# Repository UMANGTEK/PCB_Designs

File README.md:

This Repository consists of all the final versions of PCB designs made by me.

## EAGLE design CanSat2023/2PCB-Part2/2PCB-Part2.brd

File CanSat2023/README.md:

This folder consistes of the design files of flight computer for CANSAT competetion 2023. This is my first ever design of PCB which is completely designed by me me and was used on the actual cansat during launch.
Due to size restriction the computer was divided into two parts:

PART 1 - Consists of micro-controller, actuators and pins for power supply for the whole flight computer.

PART 2 - Consists of sensors operating through I2C and UART, some actuators which could fit in part 1 has also been added .

My objective while desiging this PCB was to keep microcontrollers, actuators and main power supply in same board as all actuators indivisually require independent signal from micro-controller, while I2C is a common
signal for I2C operable devices, this reduced the wires used to connect two parts. 

All the sensors used in the computer were pre fabricated, hence I did not consider the impedence while designing and worked with the default parameters. I had started working on this PCB by the end of 1-1 and wasn't aware with importance of trace width and kept an arbitary value of 0.5 mm for all connections. 

Both the PCB's are a 2 - Layered PCB, designed on free version of EAGLE software.

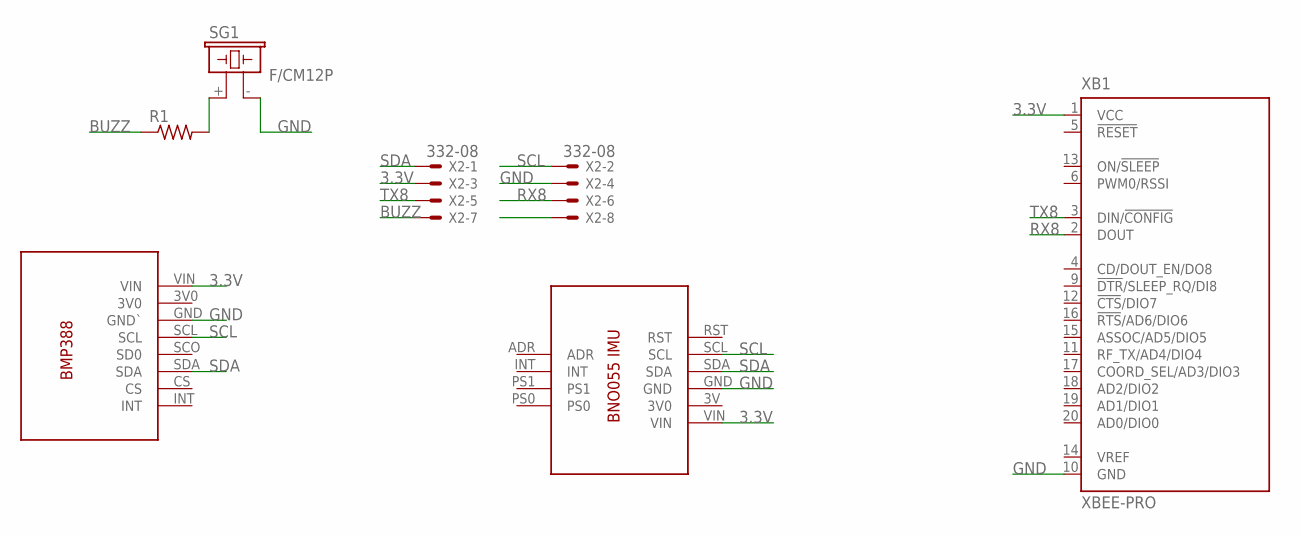
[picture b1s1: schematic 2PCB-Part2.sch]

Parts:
R1: R-US_0207/10; 0207/10
SG1: F/CM12P
U$1: BNO055
U$2: BMP388
X2: 332-08
XB1: XBEE-PRO

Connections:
3.3V: U$1.VIN, U$2.VIN, X2.3, XB1.1 (VCC)
BUZZ: R1.1, X2.7
GND: SG1.- (2), U$1.GND, U$2.GND (GND`), X2.4, XB1.10 (GND)
unnamed: R1.2, SG1.+ (1)
RX8: X2.6, XB1.2 (DOUT)
SCL: U$1.SCL, U$2.SCL, X2.2
SDA: U$1.SDA, U$2.SDA, X2.1
TX8: X2.5, XB1.3 (DIN/!CONFIG)

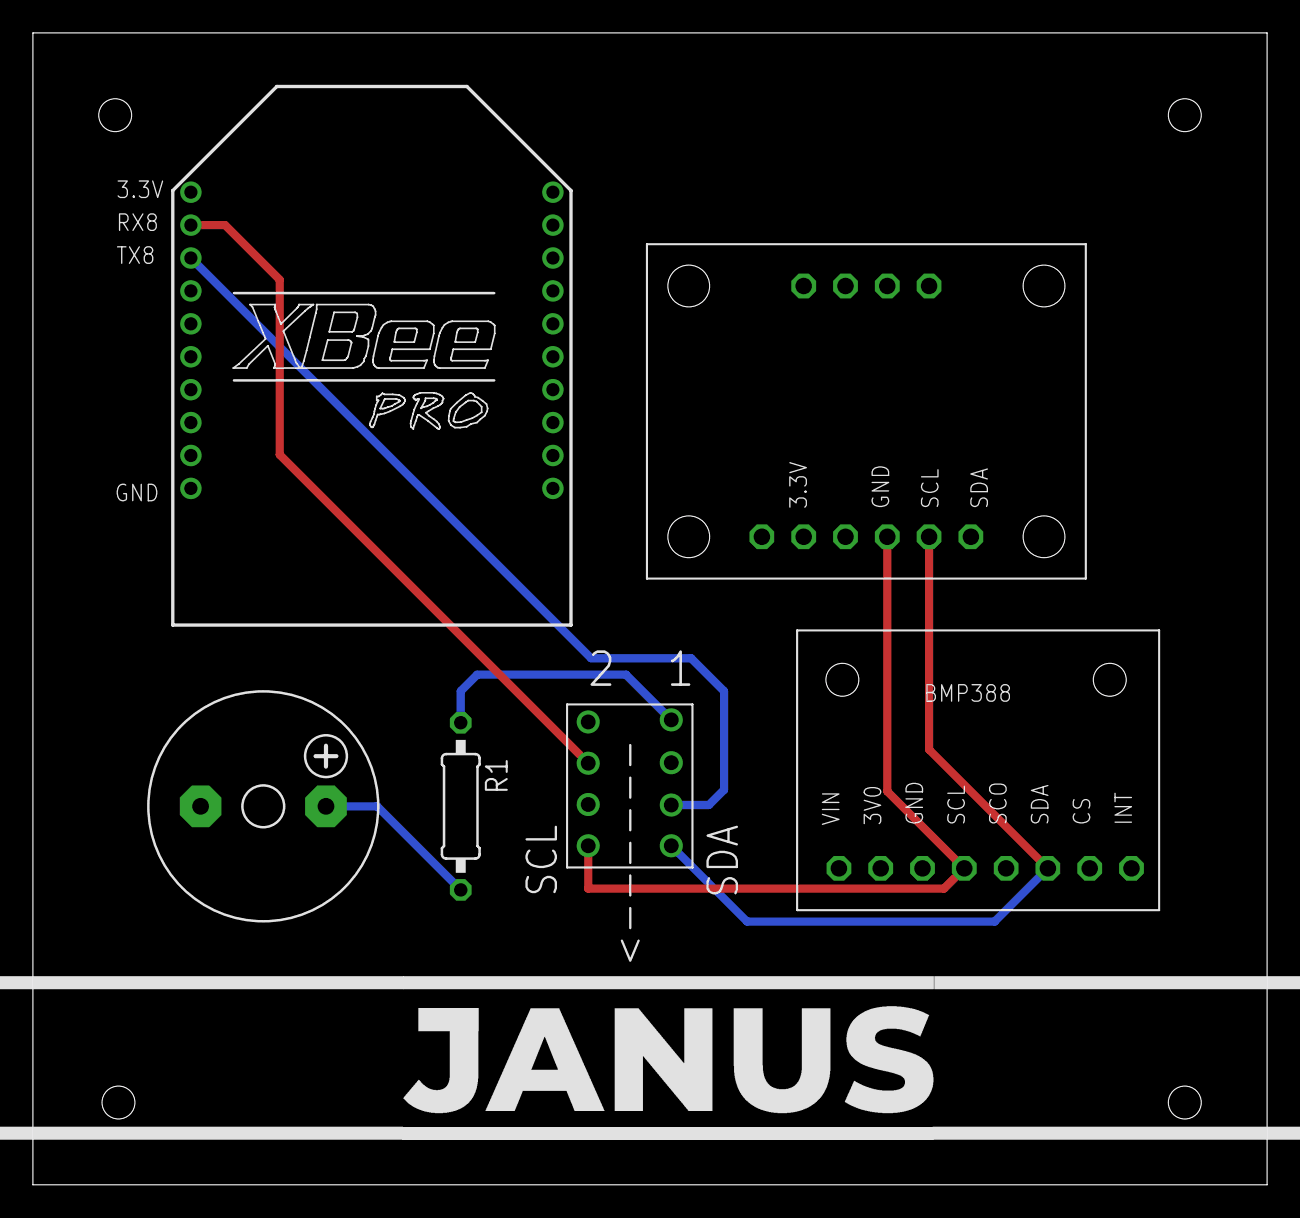
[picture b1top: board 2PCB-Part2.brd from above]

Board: 2 copper layers, 75.0 x 70.0 mm, 6 parts (0 on the bottom side), 8 nets.

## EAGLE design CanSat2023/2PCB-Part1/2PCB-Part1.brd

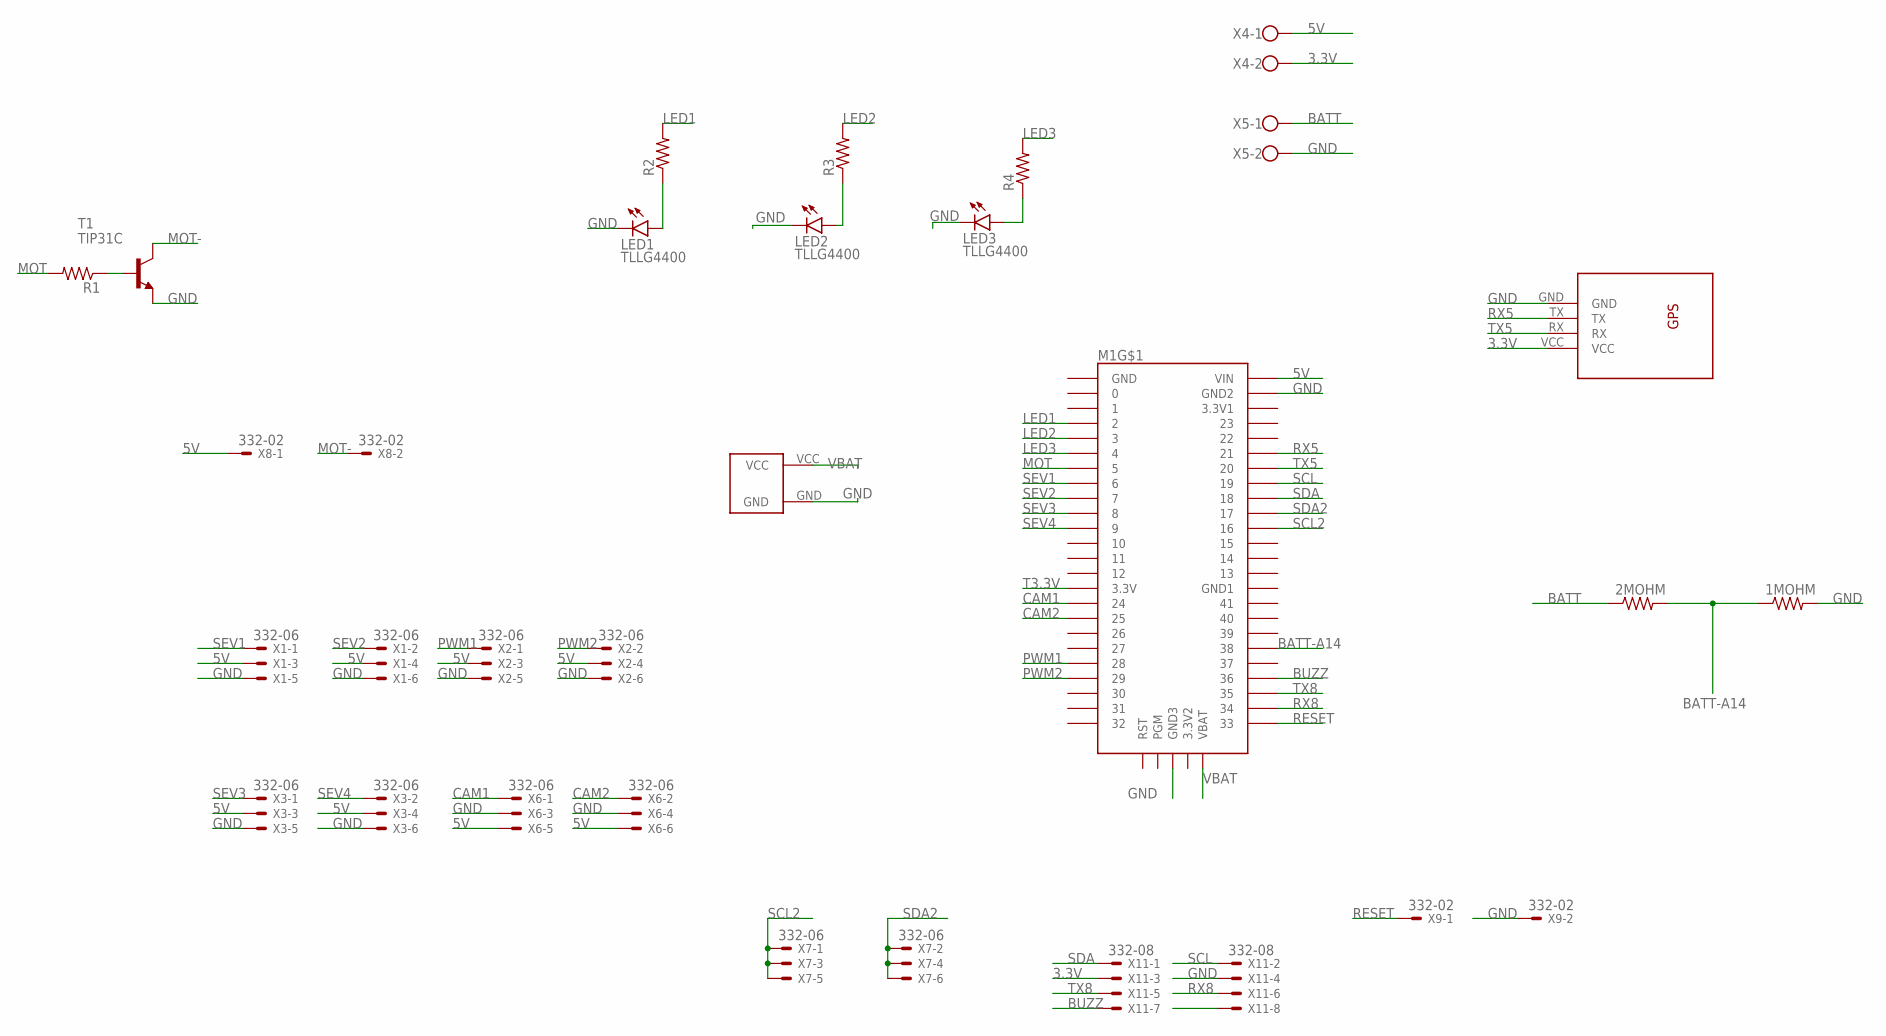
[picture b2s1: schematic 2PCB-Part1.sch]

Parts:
1MOHM, 2MOHM: R-US_0207/10; 0207/10
LED1, LED2, LED3: TLLG4400; LED3MM
M1: TEENSY4.1
R1, R2, R3, R4: R-US_0207/10; 0207/10
T1: TIP31C; TO220
U$1: GPS
U$2: CR2032; CR2032-20MM
X1, X2, X3, X6, X7: 332-06
X4, X5: W237-102
X8, X9: 332-02
X11: 332-08

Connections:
3.3V: U$1.VCC, X4.2, X11.3
5V: M1.VIN, X1.3, X1.4, X2.3, X2.4, X3.3, X3.4, X4.1, X6.5, X6.6, X8.1
BATT: 2MOHM.1, X5.1
BATT-A14: 1MOHM.1, 2MOHM.2, M1.38
BUZZ: M1.36, X11.7
CAM1: M1.24, X6.1
CAM2: M1.25, X6.2
GND: 1MOHM.2, LED1.K (C), LED2.K (C), LED3.K (C), M1.AGND (GND2), M1.GND2 (GND3), T1.3 (E), U$1.GND, U$2.GND, X1.5, X1.6, X2.5, X2.6, X3.5, X3.6, X5.2, X6.3, X6.4, X9.2, X11.4
LED1: M1.2, R2.2
LED2: M1.3, R3.2
LED3: M1.4, R4.2
MOT: M1.5, R1.2
MOT-: T1.2 (C), X8.2
unnamed: LED1.A, R2.1
unnamed: LED2.A, R3.1
unnamed: LED3.A, R4.1
unnamed: R1.1, T1.1 (B)
PWM1: M1.28, X2.1
PWM2: M1.29, X2.2
RESET: M1.33, X9.1
RX5: M1.21/A7 (21), U$1.TX
RX8: M1.34, X11.6
SCL: M1.19/A5/SCL (19), X11.2
SCL2: M1.16/A2 (16), X7.1, X7.3, X7.5
SDA: M1.18/A4/SDA (18), X11.1
SDA2: M1.17/A3 (17), X7.2, X7.4, X7.6
SEV1: M1.6, X1.1
SEV2: M1.7, X1.2
SEV3: M1.8, X3.1
SEV4: M1.9, X3.2
T3.3V: M1.3V3 (3.3V)
TX5: M1.20/A6 (20), U$1.RX
TX8: M1.35, X11.5
VBAT: M1.VBAT, U$2.VCC

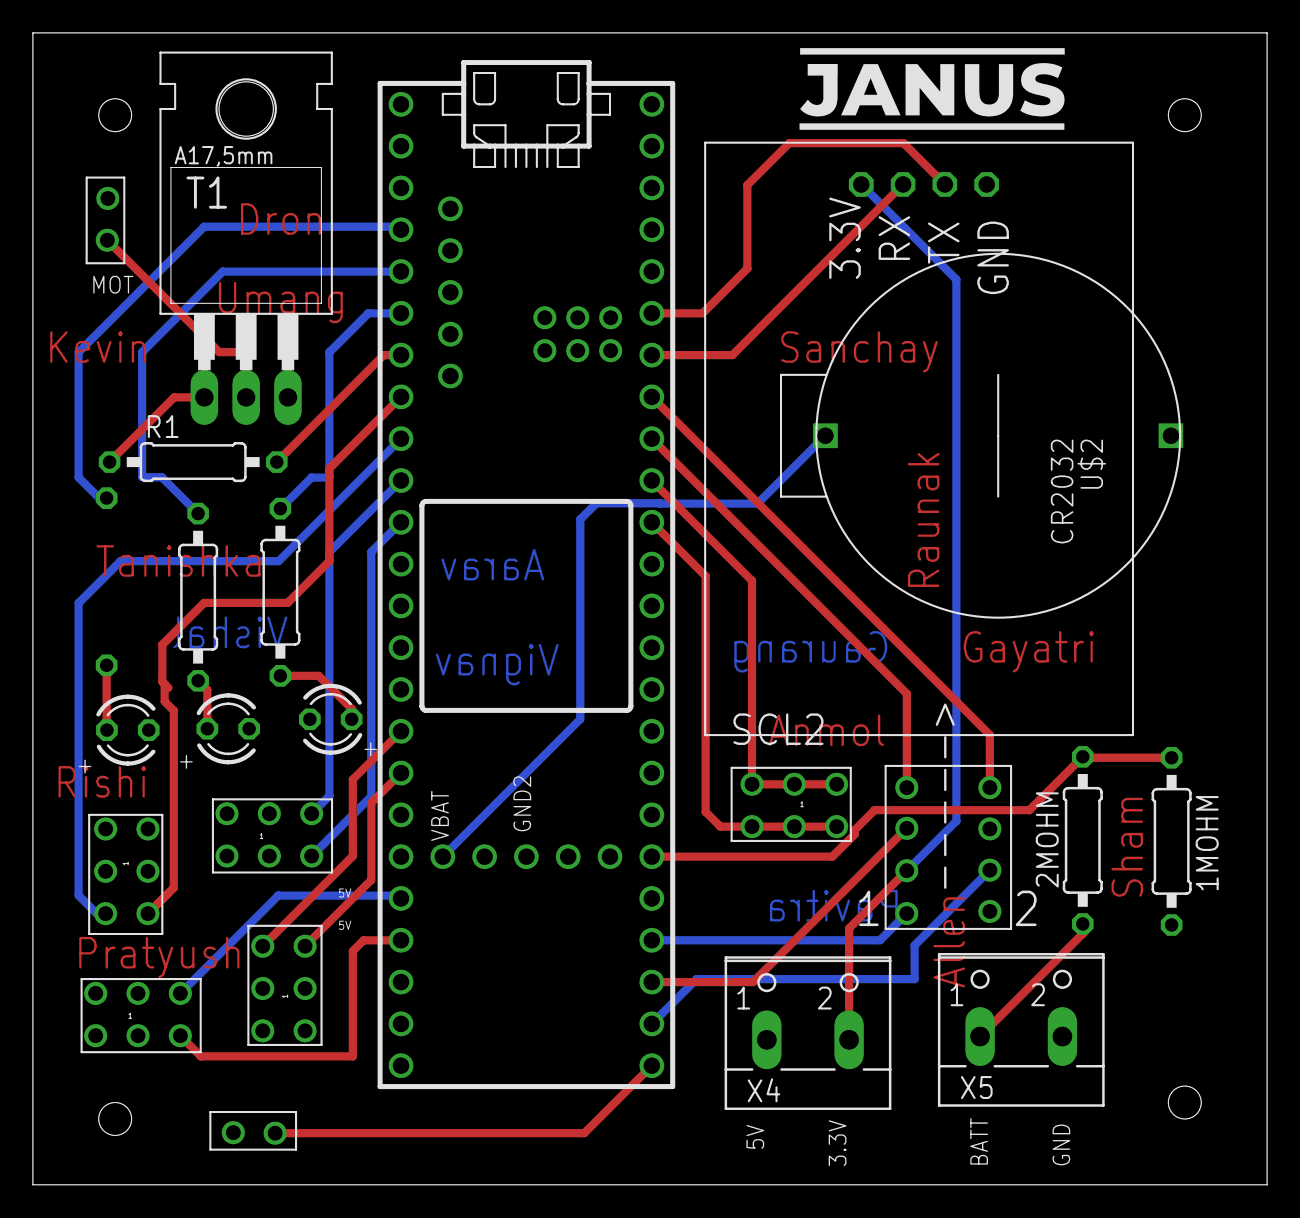
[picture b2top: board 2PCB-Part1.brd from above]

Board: 2 copper layers, 75.0 x 70.0 mm, 23 parts (1 on the bottom side), 33 nets.

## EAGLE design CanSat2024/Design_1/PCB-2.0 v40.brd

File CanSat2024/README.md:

These are the PCB designs for CanSat 2024, a total of 5 revisions were made in design. 2nd Revision was given for printing, learning from which, improvements were made and finally 5th revision was given for final print.

Design 1- This was a drastic improvement from the computer I made for 2023. This was designed in such a way that we only needed to connect battries and main switch, battery charging and power distribution components like
buck convertors were integrated in the design itself. Unlike last year, where we had to remove battry for charging and buck convertors were placed externally, this had it all on board. The battery which we were using are 
2x NCR18650B cells connected in series.

Design 2- Overall idea remained the same as design - 1 some improvements were made in connectors which made it more user friendly, and a overvoltage protection for microcontroller as also added without which the controller
kept on getting burn due to voltage rising above 3.3V as the pins were 3.3v tolerant.

This time I took care of trace width as per the current requirement for various components on board the flight computer which can be seen on design files.

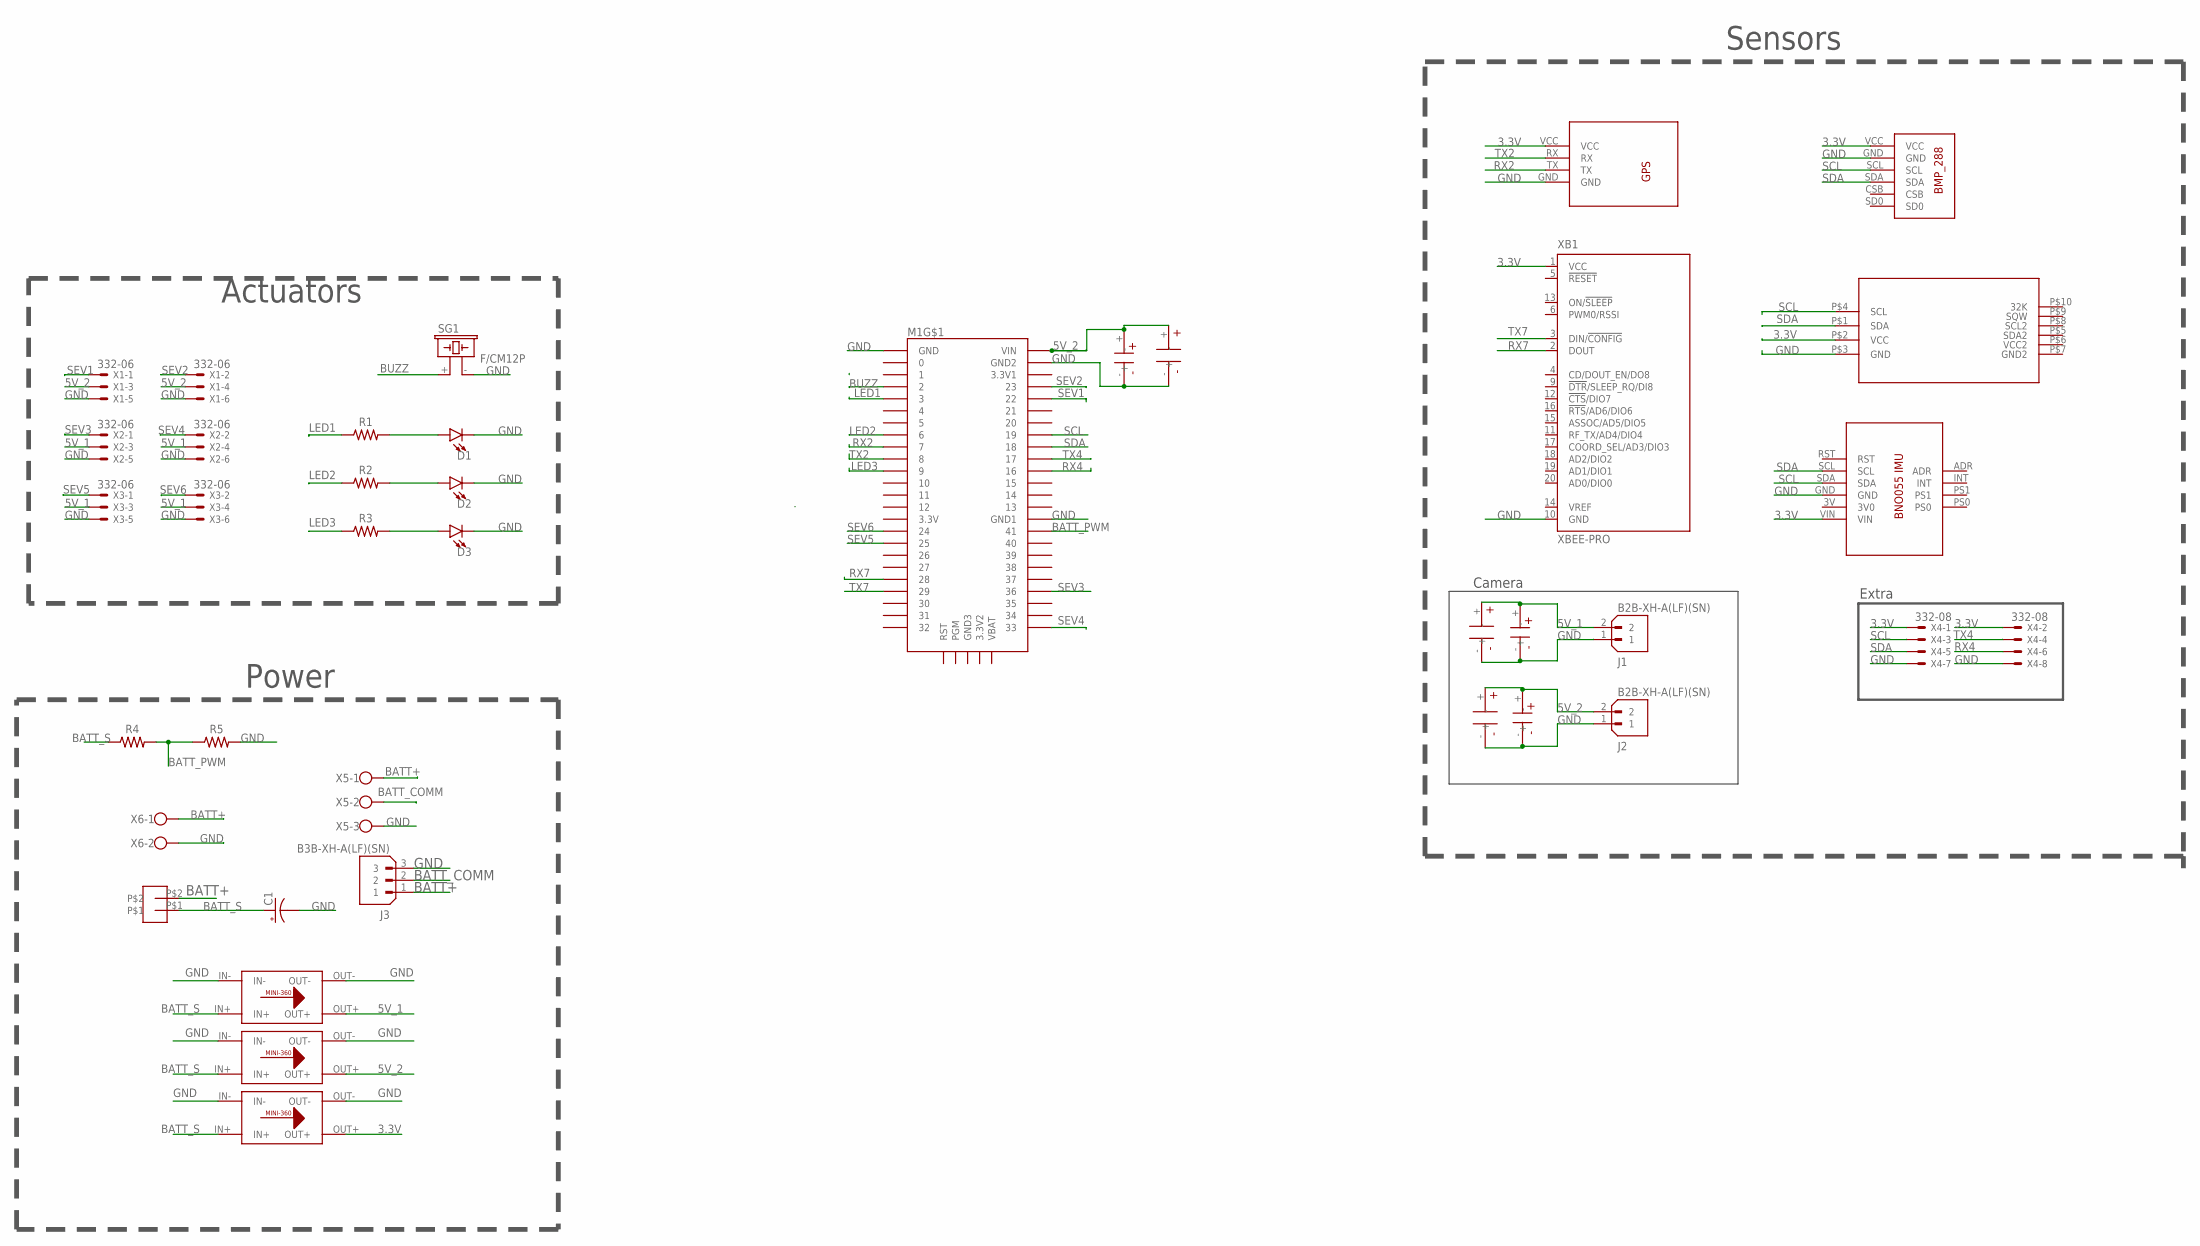
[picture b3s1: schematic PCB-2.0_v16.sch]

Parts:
C1: 1000UF-RADIAL-5MM-25V-20%-NO-SILK; CPOL-RADIAL-5MM-10MM-NS
D1, D2, D3: LED3MM; LED_3MM
J1, J2: B2B-XH-A(LF)(SN); JST_B2B-XH-A(LF)(SN)
J3: B3B-XH-A(LF)(SN); JST_B3B-XH-A(LF)(SN)
M1: TEENSY4.1
R1, R2, R3, R4, R5: R-US_AXIAL-7.2MM-PITCH; RESAD724W46L381D178B
SG1: F/CM12P
U$1: BMP_280THTOUGHHOLE; BNO055_SELF
U$2: GPS
U$3, U$5, U$6: VARY_BUCK
U$4: BNO055
U$7: DS3231_RTC
U$9: 2_PIN
U$10, U$11, U$12: 100UF-ELECTROLYTIC; 100UF_ELECTROLYTIC
U$16, U$17, U$18: 0.1UF_CERAMIC
X1, X2, X3: 332-06
X4: 332-08
X5: W237-103
X6: W237-102
XB1: XBEE-PRO

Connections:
3.3V: U$1.VCC, U$2.VCC, U$3.OUT+, U$4.VIN, U$7.P$2 (VCC), X4.1, X4.2, XB1.1 (VCC)
5V_1: J1.2, U$5.OUT+, U$10.+, U$16.+, X2.3, X2.4, X3.3, X3.4
5V_2: J2.2, M1.VIN, U$6.OUT+, U$11.+, U$12.+, U$17.+, U$18.+, X1.3, X1.4
BATT+: J3.1, U$9.P$2, X5.1, X6.1
BATT_COMM: J3.2, X5.2
BATT_PWM: M1.41, R4.2, R5.1
BATT_S: C1.+, R4.1, U$3.IN+, U$5.IN+, U$6.IN+, U$9.P$1
BUZZ: M1.2, SG1.+ (1)
GND: C1.-, D1.K (C), D2.K (C), D3.K (C), J1.1, J2.1, J3.3, M1.AGND (GND2), M1.GND, M1.GND1, R5.2, SG1.- (2), U$1.GND, U$2.GND, U$3.IN-, U$3.OUT-, U$4.GND, U$5.IN-, U$5.OUT-, U$6.IN-, U$6.OUT-, U$7.P$3 (GND), U$10.-, U$11.-, U$12.-, U$16.-, U$17.-, U$18.-, X1.5, X1.6, X2.5, X2.6, X3.5, X3.6, X4.7, X4.8, X5.3, X6.2, XB1.10 (GND)
LED1: M1.3, R1.1
LED2: M1.6, R2.1
LED3: M1.9, R3.1
unnamed: D1.A, R1.2
unnamed: D2.A, R2.2
unnamed: D3.A, R3.2
RX2: M1.7, U$2.TX
RX4: M1.16/A2 (16), X4.6
RX7: M1.28, XB1.2 (DOUT)
SCL: M1.19/A5/SCL (19), U$1.SCL, U$4.SDA, U$7.P$4 (SCL), X4.3
SDA: M1.18/A4/SDA (18), U$1.SDA, U$4.SCL, U$7.P$1 (SDA), X4.5
SEV1: M1.22/A8 (22), X1.1
SEV2: M1.23/A9 (23), X1.2
SEV3: M1.36, X2.1
SEV4: M1.33, X2.2
SEV5: M1.25, X3.1
SEV6: M1.24, X3.2
TX2: M1.8, U$2.RX
TX4: M1.17/A3 (17), X4.4
TX7: M1.29, XB1.3 (DIN/!CONFIG)

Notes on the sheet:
Actuators
Power
Sensors
Camera
Extra

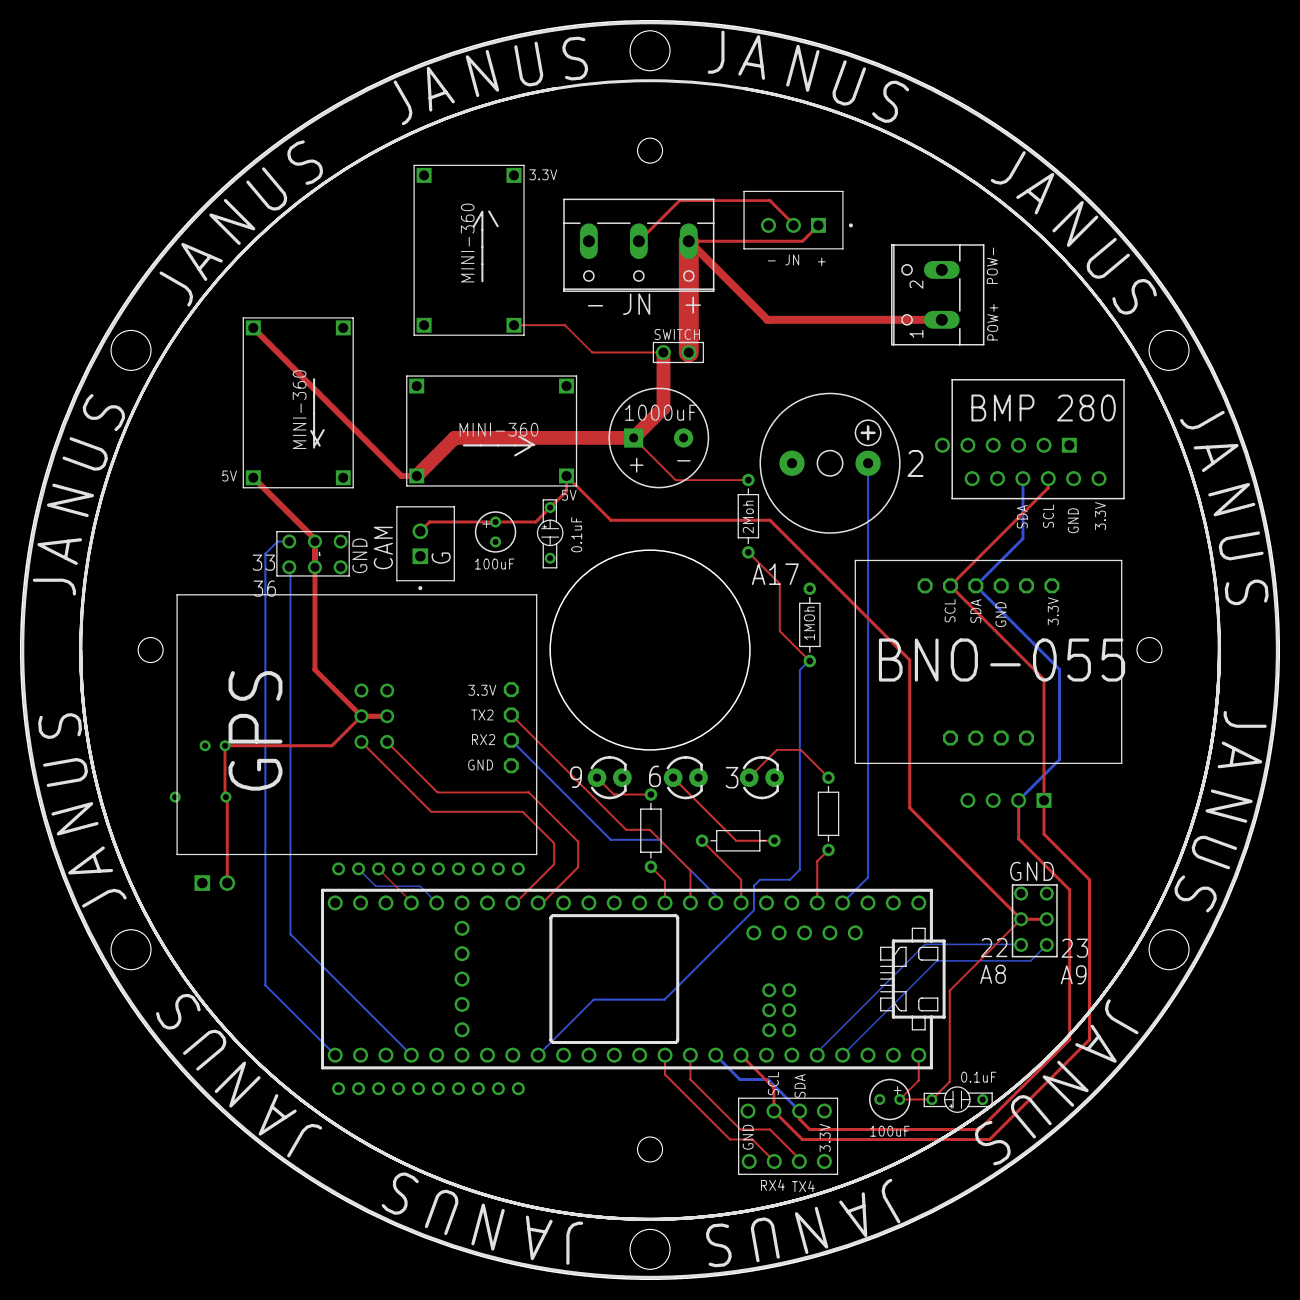
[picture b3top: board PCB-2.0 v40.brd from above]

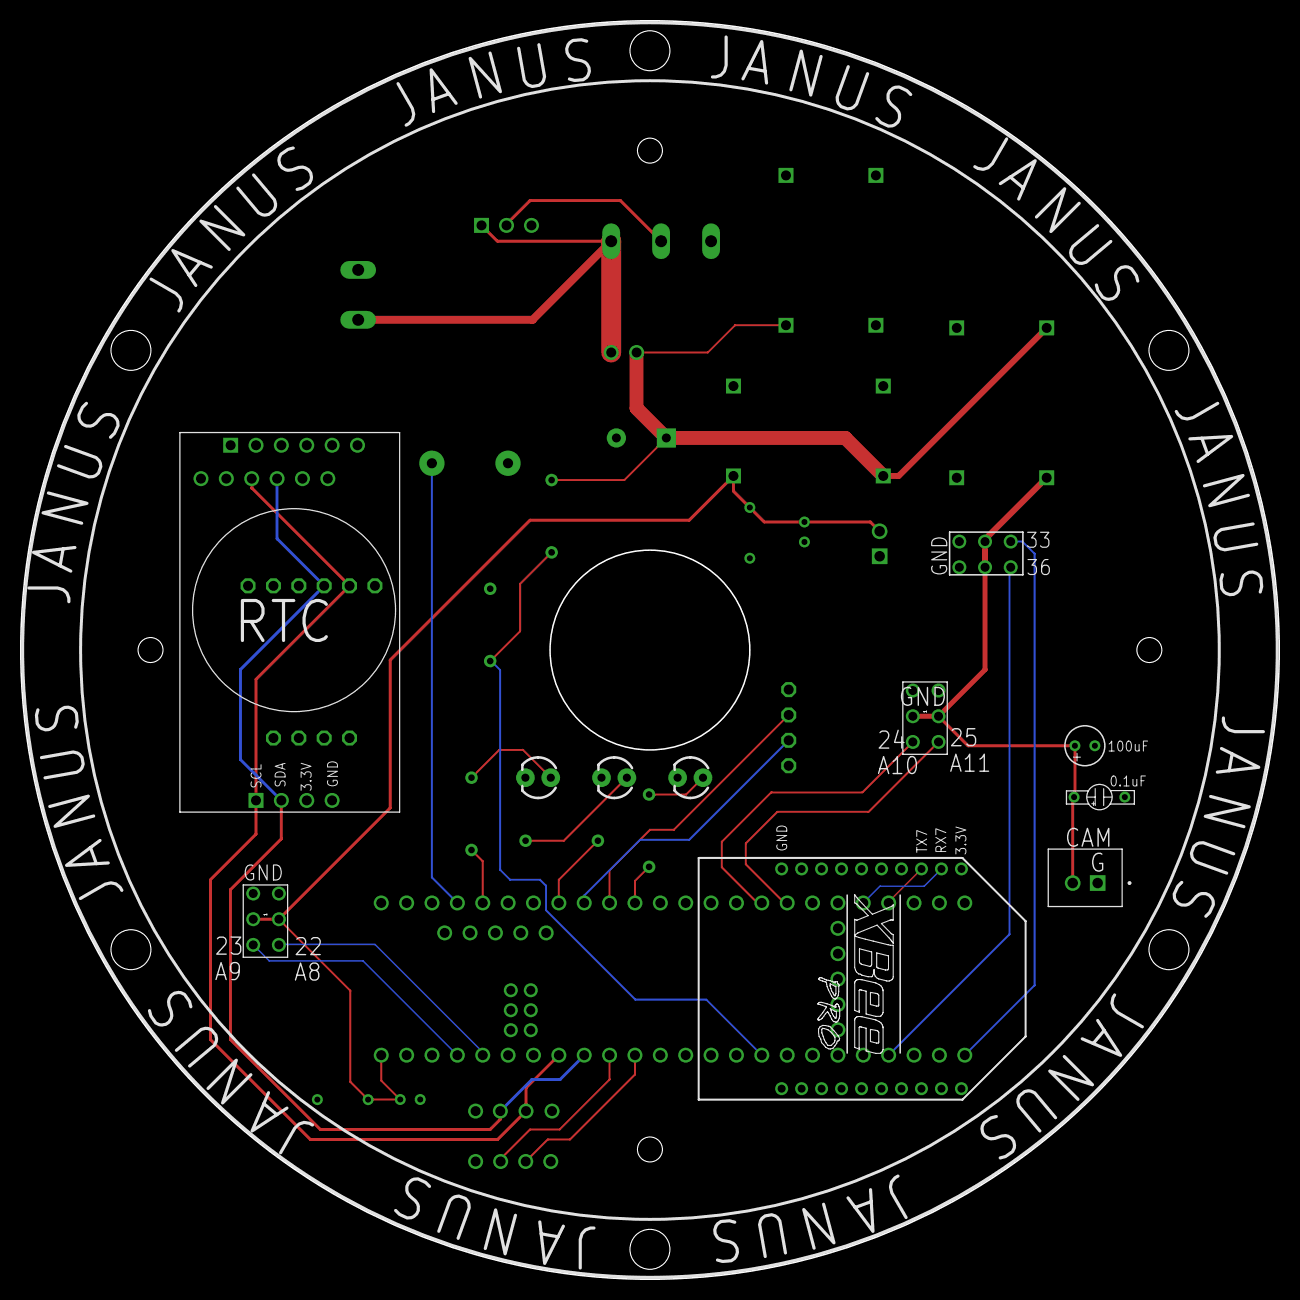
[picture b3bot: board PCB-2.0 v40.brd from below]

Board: 2 copper layers, 126.0 x 126.0 mm, 35 parts (7 on the bottom side), 29 nets.

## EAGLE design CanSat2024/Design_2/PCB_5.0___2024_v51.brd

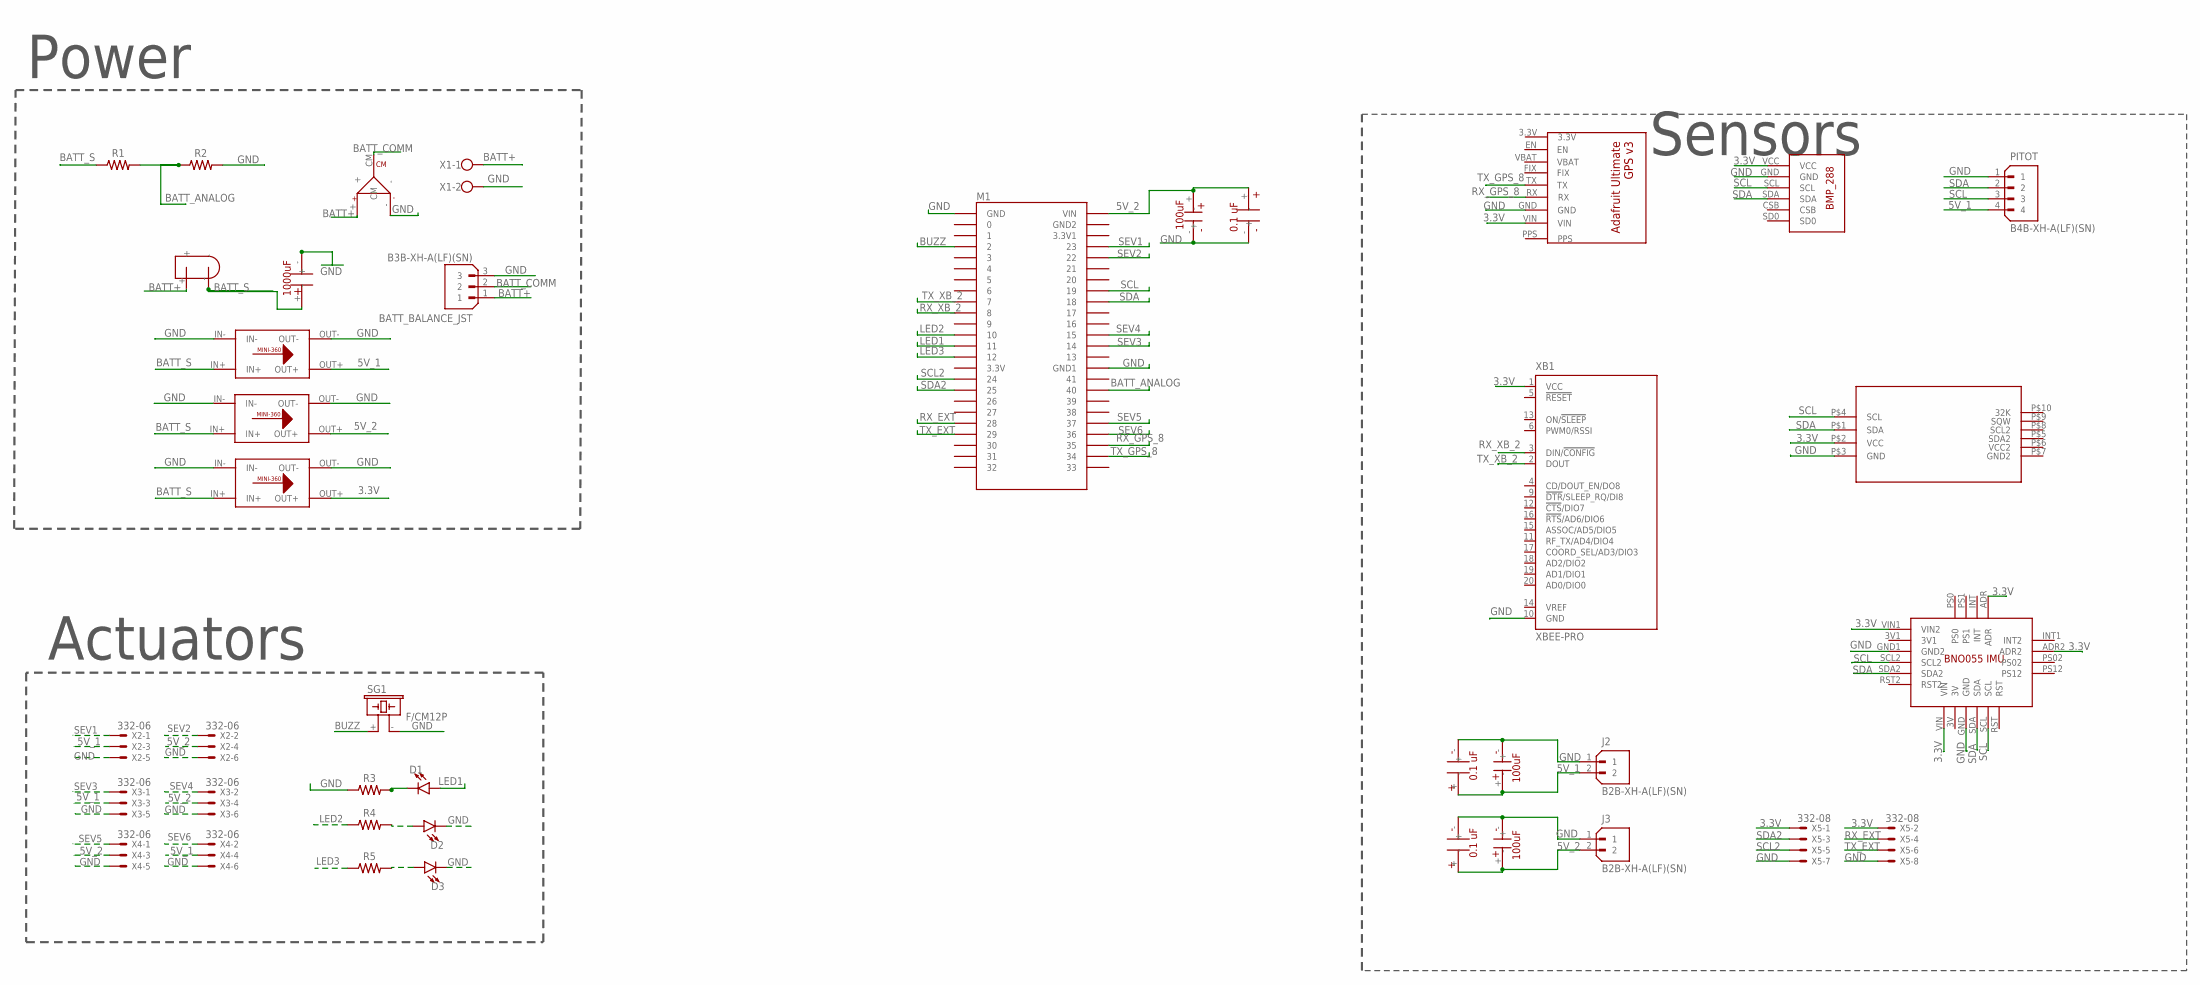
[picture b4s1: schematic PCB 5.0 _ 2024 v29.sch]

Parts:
BATT_BALANCE_JST: B3B-XH-A(LF)(SN); JST_B3B-XH-A(LF)(SN)
BATT_CONNECTOR: MT60_MALE; MT-60
D1, D2, D3: LED3MM; LED_3MM
J2, J3: B2B-XH-A(LF)(SN); JST_B2B-XH-A(LF)(SN)
M1: TEENSY4.1
PITOT: B4B-XH-A(LF)(SN); JST_B4B-XH-A(LF)(SN)
R1, R2, R3, R4, R5: R-US_AXIAL-7.2MM-PITCH; RESAD724W46L381D178B
SG1: F/CM12P
SWITCH: XT-30U
U$1: 1000UF1000UF; 1000UF
U$2: ULTIMATE_GPS; ADAFRUIT_ULTIMATE_GPS
U$3, U$4, U$5: VARY_BUCKMINI-360; VARY_BUCK
U$6: BMP_280THTOUGHHOLE; BNO055_SELF
U$7: DS3231_RTC
U$8: BNO055
U$9, U$10, U$11: 100UF-ELECTROLYTIC; 100UF_ELECTROLYTIC
U$12, U$13, U$14: 0.1UF_CERAMIC
X1: W237-102
X2, X3, X4: 332-06
X5: 332-08
XB1: XBEE-PRO

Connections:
3.3V: U$2.VIN, U$5.OUT+, U$6.VCC, U$7.P$2 (VCC), U$8.ADR, U$8.ADR2, U$8.VIN, U$8.VIN1 (VIN2), X5.1, X5.2, XB1.1 (VCC)
5V_1: J2.2, PITOT.4, U$3.OUT+, U$9.+, U$14.+, X2.3, X3.3, X4.4
5V_2: J3.2, M1.VIN, U$4.OUT+, U$10.+, U$11.+, U$12.+, U$13.+, X2.4, X3.4, X4.3
BATT+: BATT_BALANCE_JST.1, BATT_CONNECTOR.+, SWITCH.+, X1.1
BATT_ANALOG: M1.40, R1.2, R2.1
BATT_COMM: BATT_BALANCE_JST.2, BATT_CONNECTOR.CM
BATT_S: R1.1, SWITCH.-, U$1.+, U$3.IN+, U$4.IN+, U$5.IN+
BUZZ: M1.2, SG1.+ (1)
GND: BATT_BALANCE_JST.3, BATT_CONNECTOR.-, D2.K (C), D3.K (C), J2.1, J3.1, M1.GND, M1.GND1, PITOT.1, R2.2, R3.1, SG1.- (2), U$1.-, U$2.GND, U$3.IN-, U$3.OUT-, U$4.IN-, U$4.OUT-, U$5.IN-, U$5.OUT-, U$6.GND, U$7.P$3 (GND), U$8.GND, U$8.GND1 (GND2), U$9.-, U$10.-, U$11.-, U$12.-, U$13.-, U$14.-, X1.2, X2.5, X2.6, X3.5, X3.6, X4.5, X4.6, X5.7, X5.8, XB1.10 (GND)
LED1: D1.A, M1.11/MOSI (11)
LED2: M1.10/CS (10), R4.1
LED3: M1.12/MISO (12), R5.1
unnamed: D1.K (C), R3.2
unnamed: D2.A, R4.2
unnamed: D3.A, R5.2
RX_EXT: M1.28, X5.4
RX_GPS_8: M1.35, U$2.RX
RX_XB_2: M1.8, XB1.3 (DIN/!CONFIG)
SCL: M1.19/A5/SCL (19), PITOT.3, U$6.SCL, U$7.P$4 (SCL), U$8.SCL, U$8.SCL2
SCL2: M1.24, X5.5
SDA: M1.18/A4/SDA (18), PITOT.2, U$6.SDA, U$7.P$1 (SDA), U$8.SDA, U$8.SDA2
SDA2: M1.25, X5.3
SEV1: M1.23/A9 (23), X2.1
SEV2: M1.22/A8 (22), X2.2
SEV3: M1.14/A0 (14), X3.1
SEV4: M1.15/A1 (15), X3.2
SEV5: M1.37, X4.1
SEV6: M1.36, X4.2
TX_EXT: M1.29, X5.6
TX_GPS_8: M1.34, U$2.TX
TX_XB_2: M1.7, XB1.2 (DOUT)

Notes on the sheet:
Power
Sensors
Actuators

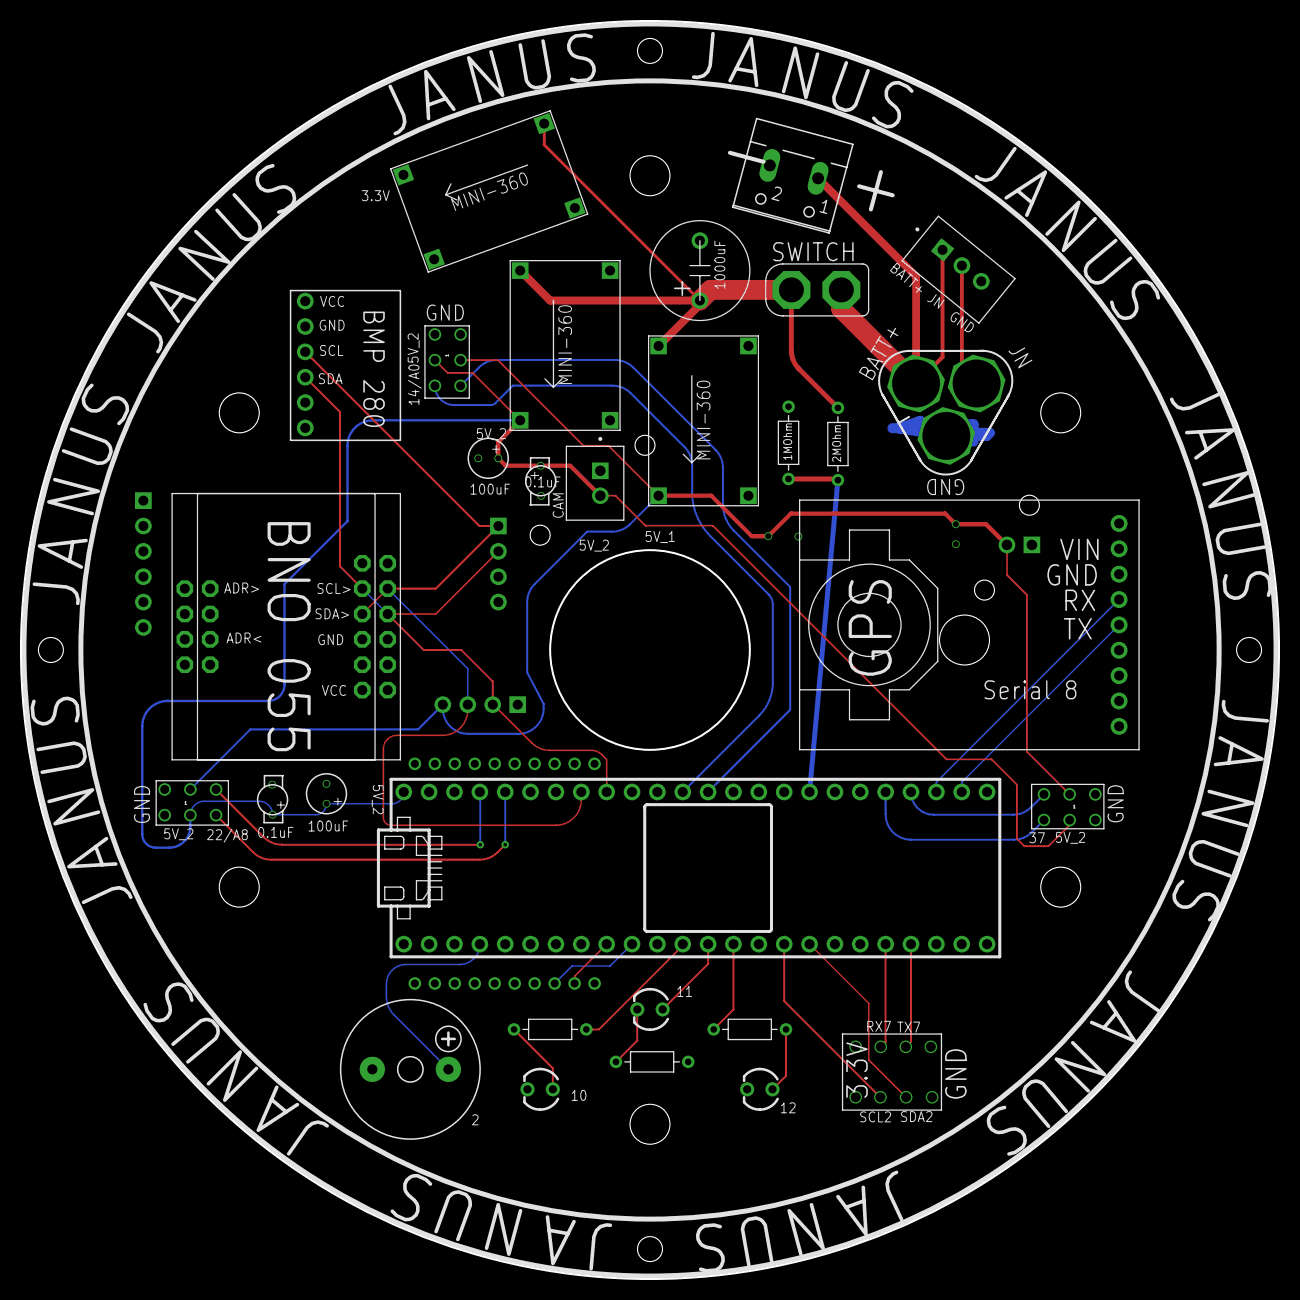
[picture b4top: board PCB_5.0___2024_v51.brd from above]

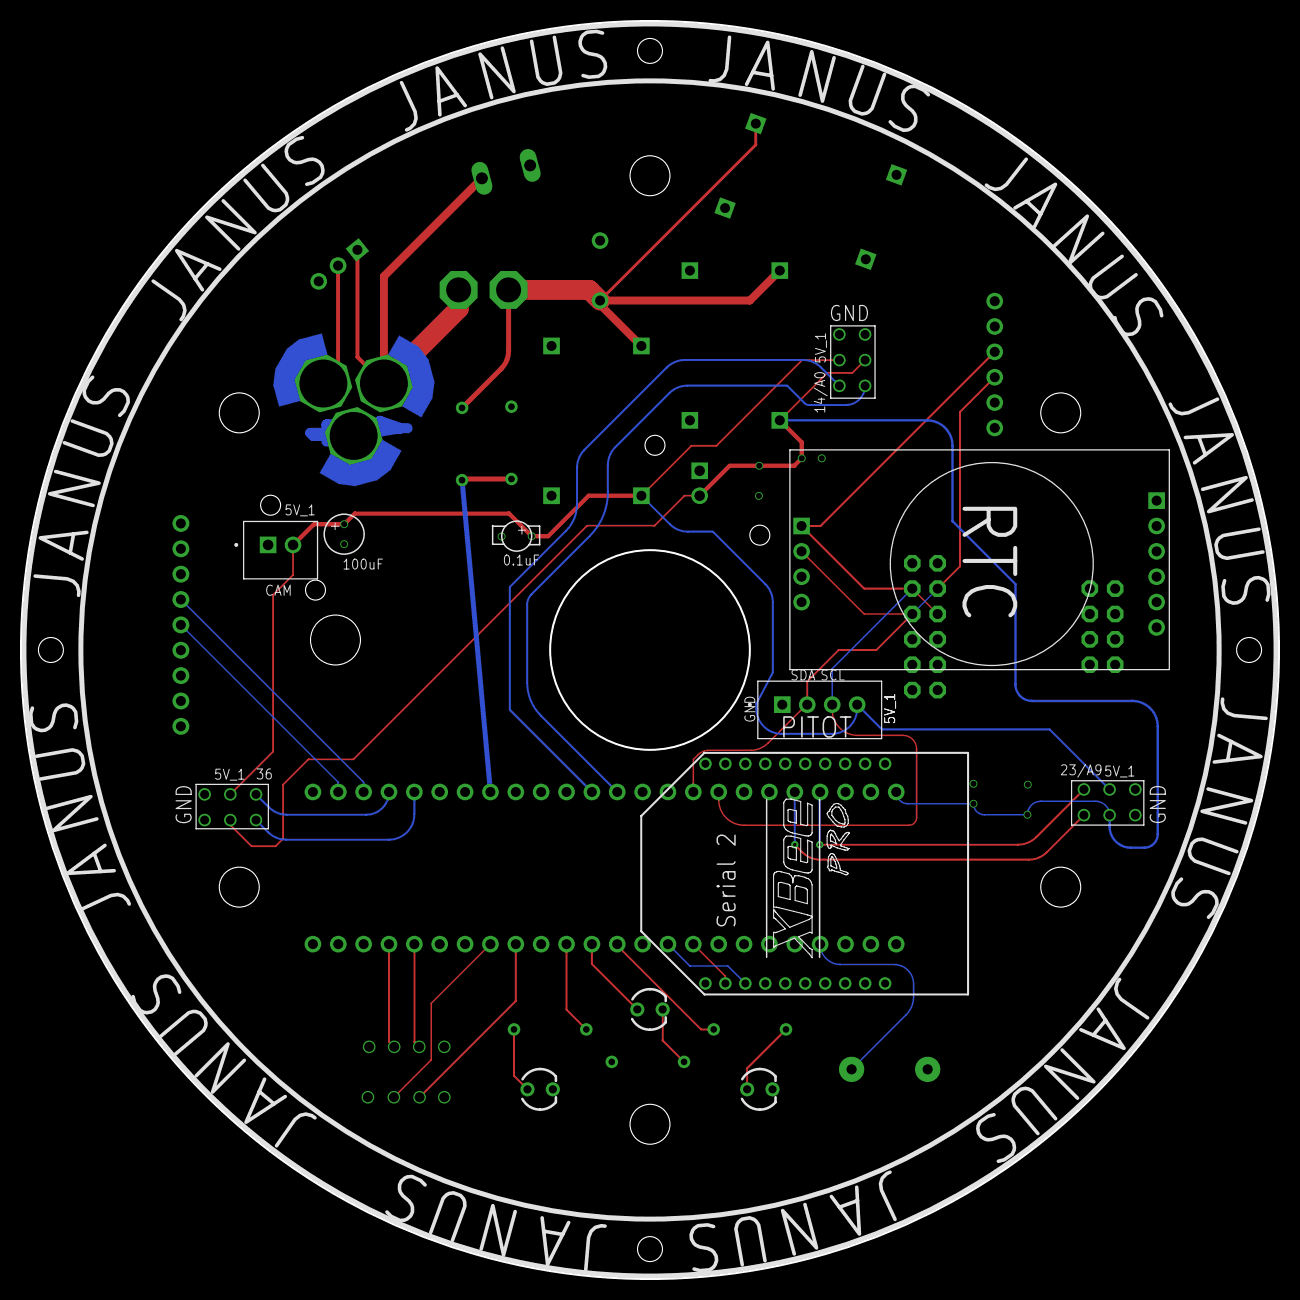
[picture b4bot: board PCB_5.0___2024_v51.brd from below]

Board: 2 copper layers, 126.0 x 126.0 mm, 36 parts (6 on the bottom side), 31 nets.

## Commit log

2024-05-26 Added the design and schematic for PCB
2024-05-26 Added README file
2024-05-26 Added README
2024-05-26 Added Part2 Design files
2024-05-26 AAdded Design_2 Flies
2024-05-26 Both version of printed design files uploaded

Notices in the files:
parts and their libraries:
SparkFun-LED: Licensing: Creative Commons ShareAlike 4.0 International - https://creativecommons.org/licenses/by-sa/4.0
